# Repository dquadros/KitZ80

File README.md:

# Kit Z80

 Este projeto tem como partida uma solicitação de um dos leitores do meu blog ([https://dqsoft.blogspot.com](https://youtube.com/@DQSoft)). Ele possui um kit dos anos 80, o CEDM-80, e gostaria de um firmware novo para ele.
 
 Para escrever o firmware o primeiro passo é ter o hardware e aí está o projeto: construir um microcomputador compatível com o CEDM-80 (versão 1, para ser mais preciso). É um projeto de médio a longo prazo, ficarei muito feliz se o concluir até a ~~metade do ano atual (2024)~~ o final do primeiro trimestre de 2026.
 
 O projeto está sendo documentado no blog e no meu canal no Youtube ([https://youtube.com/@DQSoft](https://youtube.com/@DQSoft))
 
 ## Testes do Circuito de Reset (02/06/24)
 
 Em Circuito/TesteReset está o esquema do circuito montado para testar três opções para o Reset.
 
 ## Teste do Uso do 74HC373 como Latch/Porta de Saída (13/06/24)
 
 Em Circuito/Teste373 está o esquema do circuito montado para testar o uso do 74HC373 como porta de saída.
 
 Em Programas/TstBlink está o programa usado no teste.
  
 ## Teste da  RAM (24/08/24)
 
 Em Programas/MTest está o programa, que usa o gerador de números pseudo-aleatorios do Pitfall para testar a memória RAM!
 
 ## Teste Inicial do Display (14/04/25)
 
 Com a montagem da placa de I/O iniciada, é hora de testar o circuito de acionamento do display e validar o valor dos resistores de limitação de corrente.
 
 O programa de testes está em Programas/TstDisp.
 
 ## Teste Final do Display (14/02/25)
 
 Após mais uma longa pausa, a montagem do circuito do display está completa.
 
 O programa de testes está em Programas/TstDisp.

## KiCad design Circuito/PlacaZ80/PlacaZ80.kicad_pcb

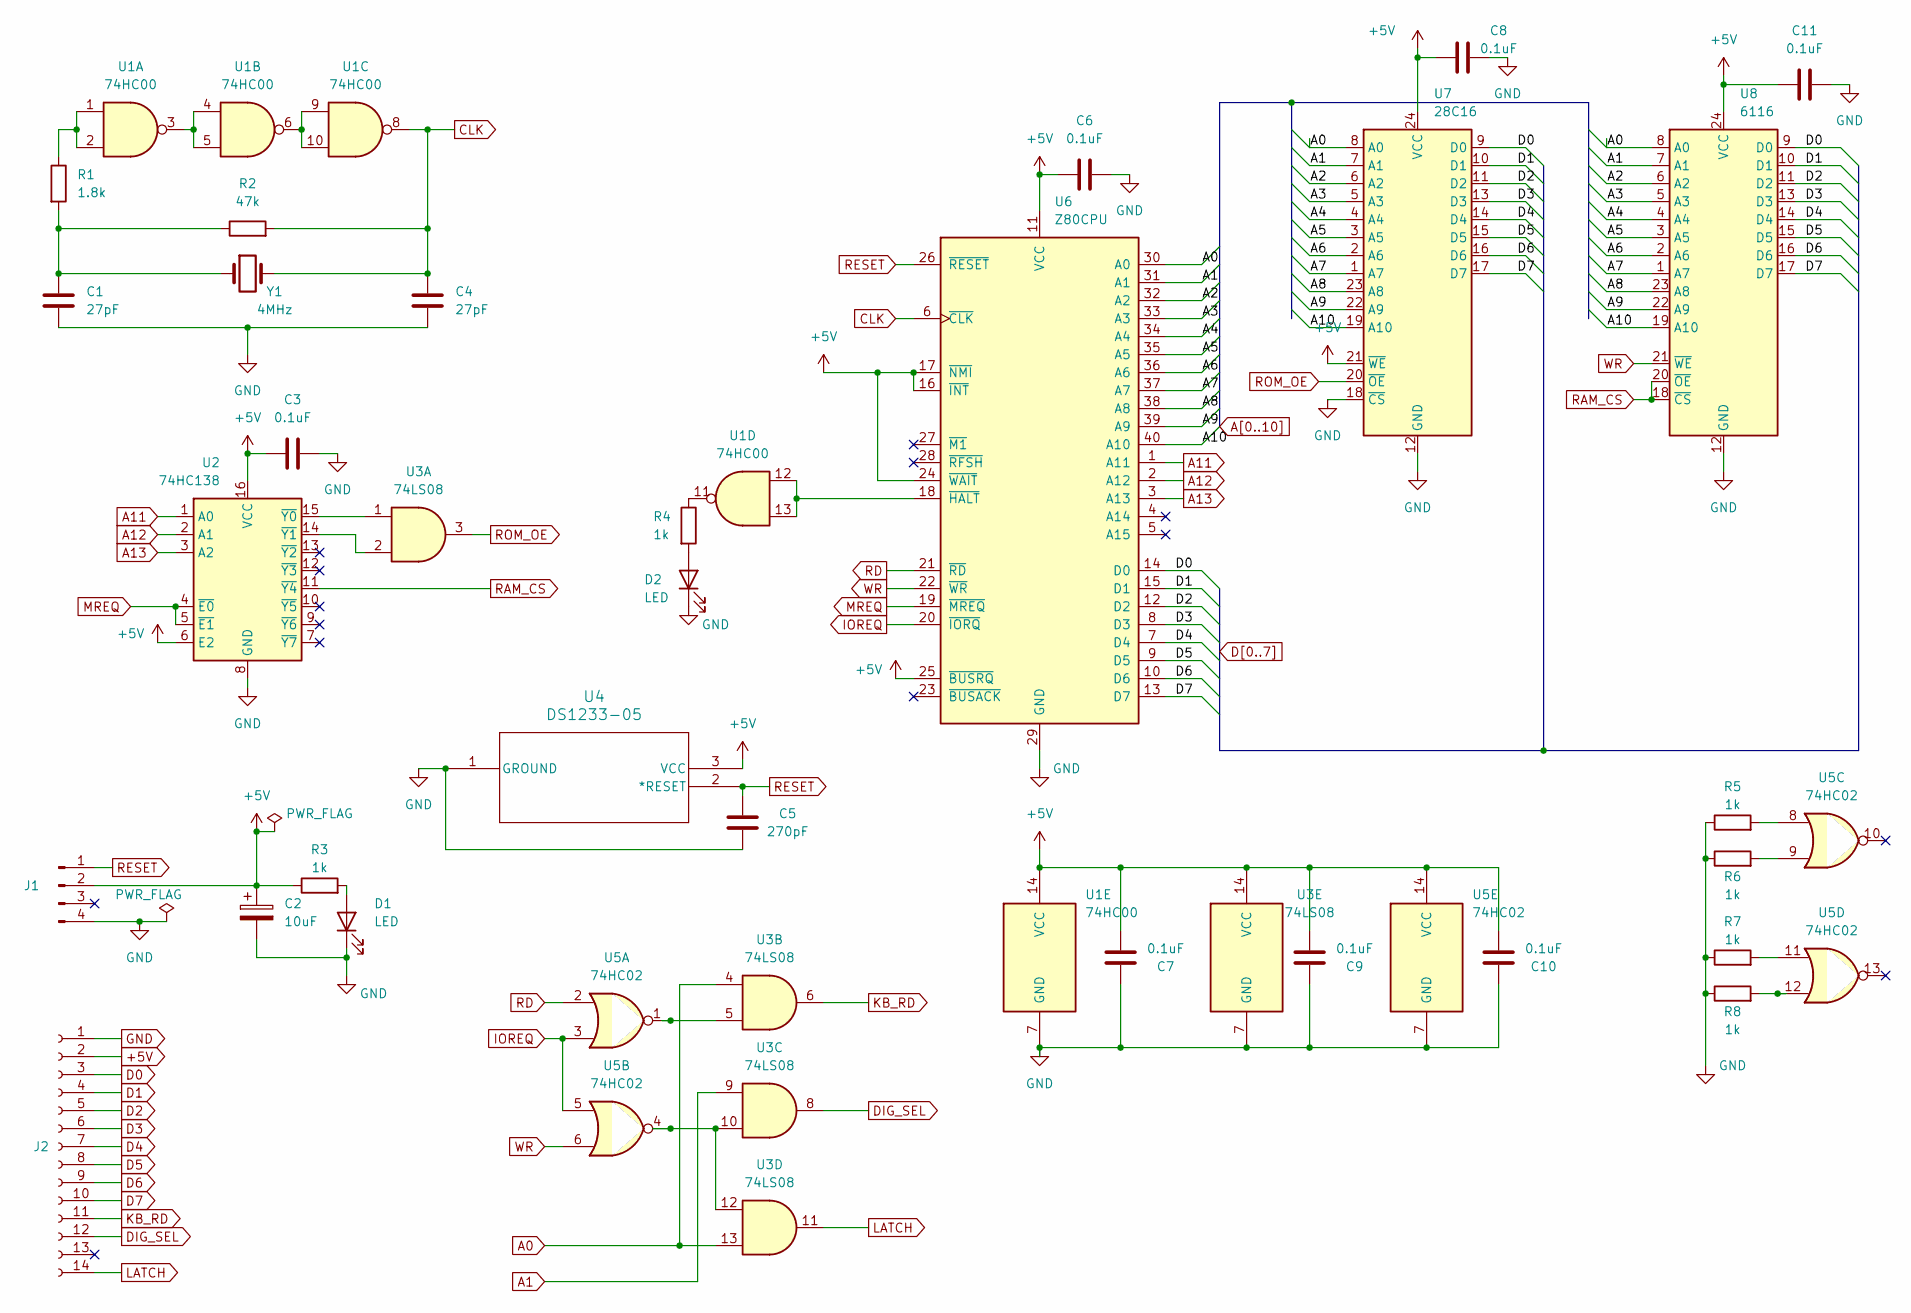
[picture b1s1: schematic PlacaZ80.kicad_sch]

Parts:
C1, C4: 27pF; C_Disc_D3.0mm_W2.0mm_P2.50mm
C2: 10uF; C_Radial_D5.0mm_H5.0mm_P2.00mm
C3, C6, C7, C8, C9, C10, C11: 0.1uF; C_Disc_D3.0mm_W2.0mm_P2.50mm
C5: 270pF; C_Disc_D3.0mm_W2.0mm_P2.50mm
D1, D2: LED; LED_D3.0mm
J1: Conn_01x04_Pin; PinHeader_1x04_P2.54mm_Horizontal
J2: Conn_01x14_Socket; PinSocket_1x14_P2.54mm_Horizontal
R1: 1.8k; R_Axial_DIN0207_L6.3mm_D2.5mm_P10.16mm_Horizontal
R2: 47k; R_Axial_DIN0207_L6.3mm_D2.5mm_P10.16mm_Horizontal
R3, R4, R5, R6, R7, R8: 1k; R_Axial_DIN0207_L6.3mm_D2.5mm_P10.16mm_Horizontal
U1: 74HC00; DIP-14_W7.62mm
U2: 74HC138; DIP-16_W7.62mm
U3: 74LS08; DIP-14_W7.62mm
U4: DS1233-05; 21-0250B_MXM
U5: 74HC02; DIP-14_W7.62mm
U6: Z80CPU; DIP-40_W15.24mm_Socket
U7: 28C16; DIP_Socket-24_W11.9_W12.7_W15.24_W17.78_W18.5_3M_224-1275-0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
U8: 6116; DIP-24_W15.24mm_Socket
Y1: 4MHz; Crystal_HC49-U_Vertical

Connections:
+5V: C2.1, C3.1, C6.1, C7.1, C8.1, C9.1, C10.1, C11.1, J1.2, J2.2, R3.1, U1.14 (VCC), U2.6 (E2), U2.16 (VCC), U3.14 (VCC), U4.3 (VCC), U5.14 (VCC), U6.11 (VCC), U6.16 (~INT), U6.17 (~NMI), U6.24 (~WAIT), U6.25 (~BUSRQ), U7.21 (~WE), U7.24 (VCC), U8.24 (VCC)
A0: U3.4, U3.13, U6.30 (A0), U7.8 (A0), U8.8 (A0)
A1: U3.9, U6.31 (A1), U7.7 (A1), U8.7 (A1)
A2: U6.32 (A2), U7.6 (A2), U8.6 (A2)
A3: U6.33 (A3), U7.5 (A3), U8.5 (A3)
A4: U6.34 (A4), U7.4 (A4), U8.4 (A4)
A5: U6.35 (A5), U7.3 (A5), U8.3 (A5)
A6: U6.36 (A6), U7.2 (A6), U8.2 (A6)
A7: U6.37 (A7), U7.1 (A7), U8.1 (A7)
A8: U6.38 (A8), U7.23 (A8), U8.23 (A8)
A9: U6.39 (A9), U7.22 (A9), U8.22 (A9)
A10: U6.40 (A10), U7.19 (A10), U8.19 (A10)
A11: U2.1 (A0), U6.1 (A11)
A12: U2.2 (A1), U6.2 (A12)
A13: U2.3 (A2), U6.3 (A13)
CLK: C4.1, R2.2, U1.8, U6.6 (~CLK), Y1.2
D0: J2.3, U6.14 (D0), U7.9 (D0), U8.9 (D0)
D1: J2.4, U6.15 (D1), U7.10 (D1), U8.10 (D1)
D2: J2.5, U6.12 (D2), U7.11 (D2), U8.11 (D2)
D3: J2.6, U6.8 (D3), U7.13 (D3), U8.13 (D3)
D4: J2.7, U6.7 (D4), U7.14 (D4), U8.14 (D4)
D5: J2.8, U6.9 (D5), U7.15 (D5), U8.15 (D5)
D6: J2.9, U6.10 (D6), U7.16 (D6), U8.16 (D6)
D7: J2.10, U6.13 (D7), U7.17 (D7), U8.17 (D7)
DIG_SEL: J2.12, U3.8
GND: C1.2, C2.2, C3.2, C4.2, C5.2, C6.2, C7.2, C8.2, C9.2, C10.2, C11.2, D1.1 (K), D2.1 (K), J1.4, J2.1, R5.1, R6.1, R7.1, R8.1, U1.7 (GND), U2.8 (GND), U3.7 (GND), U4.1 (GROUND), U5.7 (GND), U6.29 (GND), U7.12 (GND), U7.18 (~CS), U8.12 (GND)
IOREQ: U5.3, U5.5, U6.20 (~IORQ)
KB_RD: J2.11, U3.6
LATCH: J2.14, U3.11
MREQ: U2.4 (~E0), U2.5 (~E1), U6.19 (~MREQ)
unnamed: C1.1, R1.2, R2.1, Y1.1
unnamed: D1.2 (A), R3.2
unnamed: D2.2 (A), R4.2
unnamed: R1.1, U1.1, U1.2
unnamed: R4.1, U1.11
unnamed: R5.2, U5.8
unnamed: R6.2, U5.9
unnamed: R7.2, U5.11
unnamed: R8.2, U5.12
unnamed: U1.3, U1.4, U1.5
unnamed: U1.6, U1.9, U1.10
unnamed: U2.15 (~Y0), U3.1
unnamed: U2.14 (~Y1), U3.2
unnamed: U3.5, U5.1
unnamed: U3.10, U3.12, U5.4
unnamed: U1.12, U1.13, U6.18 (~HALT)
RAM_CS: U2.11 (~Y4), U8.18 (~CS), U8.20 (~OE)
RD: U5.2, U6.21 (~RD)
RESET: C5.1, J1.1, U4.2 (*RESET), U6.26 (~RESET)
ROM_OE: U3.3, U7.20 (~OE)
WR: U5.6, U6.22 (~WR), U8.21 (~WE)

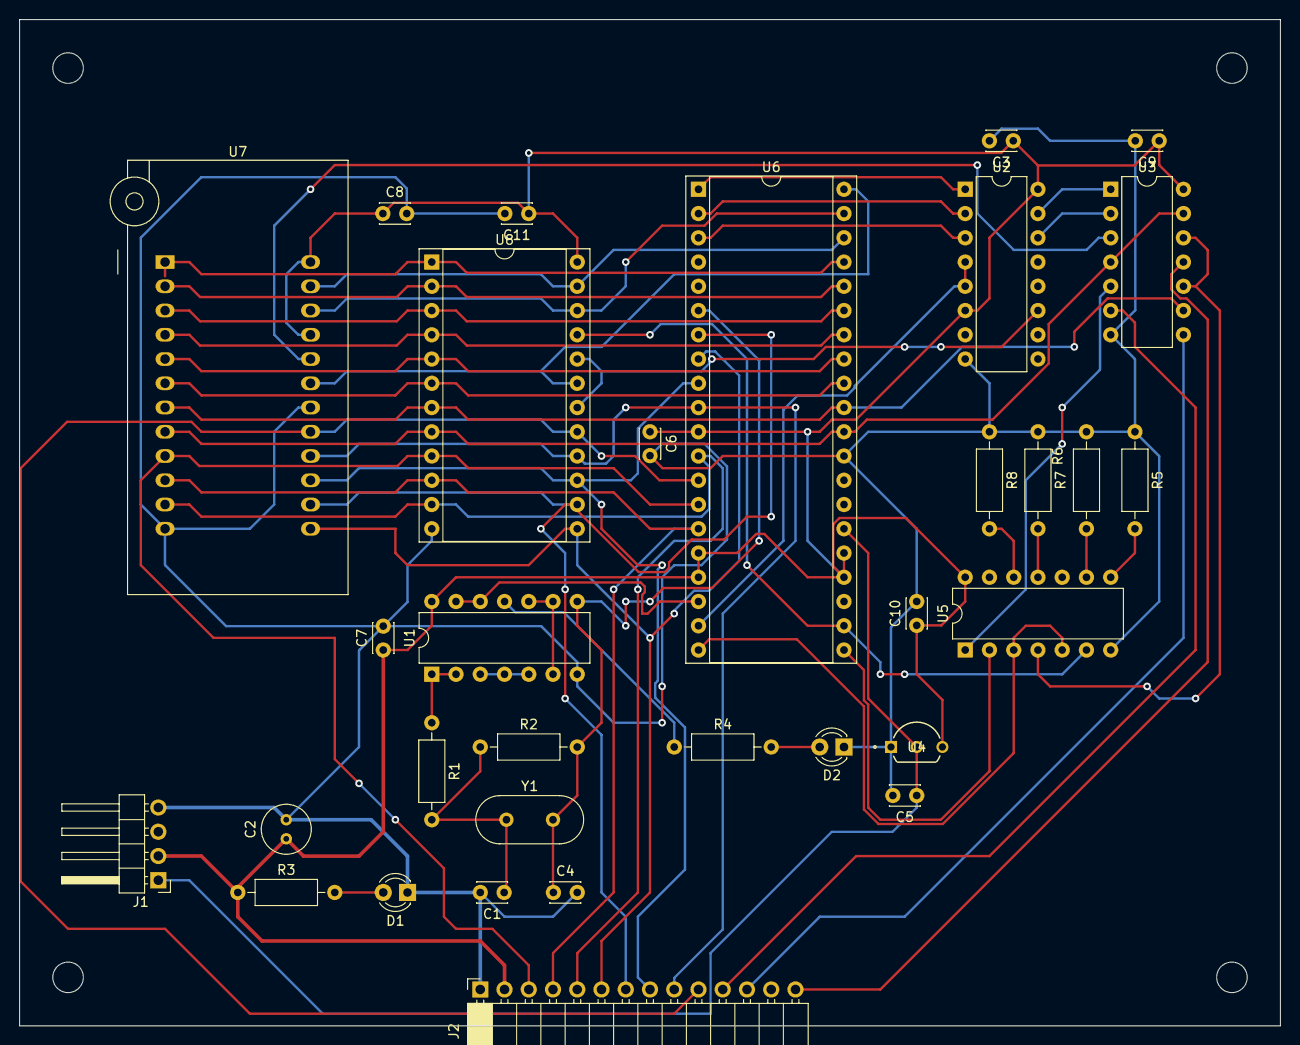
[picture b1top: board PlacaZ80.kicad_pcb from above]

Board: 2 copper layers, 132.1 x 105.4 mm, 32 parts (0 on the bottom side), 51 nets.

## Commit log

2024-06-02 Inclusão do circuito de reset
2024-06-13 Acrescentado teste do 74HC373
2024-08-26 Montagem e teste da placa CPU
2026-02-14 Acréscimo da Placa de IO e o teste do Display
